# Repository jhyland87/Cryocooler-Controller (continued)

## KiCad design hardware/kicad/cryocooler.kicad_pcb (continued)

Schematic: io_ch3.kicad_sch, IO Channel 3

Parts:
C449: 100nF; C_0402_1005Metric
C450, C451: 1uF/50V; C_1206_3216Metric
D115, D116: TVS1800DRVR; WSON-6-1EP_2x2mm_P0.65mm_EP1x1.6mm
J38: IO3 (V+ / IO / GND / NC); XKB_X2510WRS-04-9TSN_1x04_P2.54mm_Horizontal
JP16: IO3 5V; R_0603_1608Metric
JP17: IO3 12V; R_0603_1608Metric; not fitted
Q103: CSD17381F4; Texas_FemtoFET_F4_1.0x0.6mm
R676, R683: 100k; R_0402_1005Metric
R677: 20k; R_0402_1005Metric
R678: 120; R_2512_6332Metric
R679: 1M; R_0402_1005Metric
R680: 53.6k; R_0402_1005Metric
R681: 10k; R_0402_1005Metric
R682: 22k; R_0402_1005Metric
U121: TPS26625DRCR; Texas_DRC0010J

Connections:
+3V3: R681.1; also elsewhere on the board
+5V: JP16.1 (A); also elsewhere on the board
+12V: JP17.1 (A); also elsewhere on the board
/Universal IO/IO3_ADC: C449.1, R676.2, R677.1; also elsewhere on the board
/Universal IO/IO3_BURDEN: Q103.1 (G), R683.1; also elsewhere on the board
/Universal IO/IO3_DIV: R677.2; also elsewhere on the board
/Universal IO/IO3_PIN: D116.4 (IN), D116.5 (IN), D116.6 (IN), J38.2, R676.1, R678.1; also elsewhere on the board
/Universal IO/IO3_SENS_EN: R682.1, U121.4 (~SHDN); also elsewhere on the board
/Universal IO/~IO3_SENS_FLT: R681.2, U121.9 (~FLT); also elsewhere on the board
GND: C449.2, C450.2, C451.2, D115.1 (GND), D115.2 (GND), D115.3 (GND), D115.7 (GND), D116.1 (GND), D116.2 (GND), D116.3 (GND), D116.7 (GND), J38.3, Q103.2 (S), R680.2, R682.2, R683.2, U121.3 (OVP), U121.5 (RTN), U121.6 (GND), U121.11 (EP); also elsewhere on the board
unnamed: C451.1, D115.4 (IN), D115.5 (IN), D115.6 (IN), J38.1, U121.10 (OUT)
unnamed: C450.1, JP16.2 (B), JP17.2 (B), R679.1, U121.1 (IN)
unnamed: Q103.3 (D), R678.2
unnamed: R680.1, U121.7 (ILIM)
unnamed: R679.2, U121.2 (UVLO)

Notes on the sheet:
Input: the pin through 100k to the ADC; with the 20k leg grounded (default) 15 V reads 2.5 V, with DIRECT high the range is 0-2.5 V. BURDEN adds 120 R for 4-20 mA loops; PULLUP (range switch sheet) adds 10k to +3V3.
SENSOR SUPPLY AND CONNECTOR
Universal I/O channel 3: connector pin 1 = switched sensor supply, 2 = signal, 3 = GND. Output: DAC level x 4.83 from a TSB582 section through a switch (IO Output Drivers sheet), up to 100 mA, open while OUT_EN is low.
Every control line is pulled to its off level, so the channel is high impedance with the sensor supply off until firmware sets the expander.
MEASUREMENT

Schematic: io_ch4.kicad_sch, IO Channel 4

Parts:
C452: 100nF; C_0402_1005Metric
C453, C454: 1uF/50V; C_1206_3216Metric
D117, D118: TVS1800DRVR; WSON-6-1EP_2x2mm_P0.65mm_EP1x1.6mm
J39: IO4 (V+ / IO / GND / NC); XKB_X2510WRS-04-9TSN_1x04_P2.54mm_Horizontal
JP18: IO4 5V; R_0603_1608Metric
JP19: IO4 12V; R_0603_1608Metric; not fitted
Q104: CSD17381F4; Texas_FemtoFET_F4_1.0x0.6mm
R684, R691: 100k; R_0402_1005Metric
R685: 20k; R_0402_1005Metric
R686: 120; R_2512_6332Metric
R687: 1M; R_0402_1005Metric
R688: 53.6k; R_0402_1005Metric
R689: 10k; R_0402_1005Metric
R690: 22k; R_0402_1005Metric
U122: TPS26625DRCR; Texas_DRC0010J

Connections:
+3V3: R689.1; also elsewhere on the board
+5V: JP18.1 (A); also elsewhere on the board
+12V: JP19.1 (A); also elsewhere on the board
/Universal IO/IO4_ADC: C452.1, R684.2, R685.1; also elsewhere on the board
/Universal IO/IO4_BURDEN: Q104.1 (G), R691.1; also elsewhere on the board
/Universal IO/IO4_DIV: R685.2; also elsewhere on the board
/Universal IO/IO4_PIN: D118.4 (IN), D118.5 (IN), D118.6 (IN), J39.2, R684.1, R686.1; also elsewhere on the board
/Universal IO/IO4_SENS_EN: R690.1, U122.4 (~SHDN); also elsewhere on the board
/Universal IO/~IO4_SENS_FLT: R689.2, U122.9 (~FLT); also elsewhere on the board
GND: C452.2, C453.2, C454.2, D117.1 (GND), D117.2 (GND), D117.3 (GND), D117.7 (GND), D118.1 (GND), D118.2 (GND), D118.3 (GND), D118.7 (GND), J39.3, Q104.2 (S), R688.2, R690.2, R691.2, U122.3 (OVP), U122.5 (RTN), U122.6 (GND), U122.11 (EP); also elsewhere on the board
unnamed: C454.1, D117.4 (IN), D117.5 (IN), D117.6 (IN), J39.1, U122.10 (OUT)
unnamed: C453.1, JP18.2 (B), JP19.2 (B), R687.1, U122.1 (IN)
unnamed: Q104.3 (D), R686.2
unnamed: R688.1, U122.7 (ILIM)
unnamed: R687.2, U122.2 (UVLO)

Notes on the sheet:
MEASUREMENT
SENSOR SUPPLY AND CONNECTOR
Universal I/O channel 4: connector pin 1 = switched sensor supply, 2 = signal, 3 = GND. Output: DAC level x 4.83 from a TSB582 section through a switch (IO Output Drivers sheet), up to 100 mA, open while OUT_EN is low.
Every control line is pulled to its off level, so the channel is high impedance with the sensor supply off until firmware sets the expander.
Input: the pin through 100k to the ADC; with the 20k leg grounded (default) 15 V reads 2.5 V, with DIRECT high the range is 0-2.5 V. BURDEN adds 120 R for 4-20 mA loops; PULLUP (range switch sheet) adds 10k to +3V3.

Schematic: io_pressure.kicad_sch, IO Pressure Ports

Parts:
C432, C433: 10nF; C_0402_1005Metric
D107, D108: TVS1800DRVR; WSON-6-1EP_2x2mm_P0.65mm_EP1x1.6mm
J32: PRESSURE 1 (5V / SIG / GND / NC); XKB_X2510WRS-04-9TSN_1x04_P2.54mm_Horizontal
J33: PRESSURE 2 (5V / SIG / GND / NC); XKB_X2510WRS-04-9TSN_1x04_P2.54mm_Horizontal
R636, R638: 2.2k; R_0402_1005Metric
R637, R639: 100k; R_0402_1005Metric

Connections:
/Universal IO/IO Pressure Ports/PRESS1_PIN: D107.4 (IN), D107.5 (IN), D107.6 (IN), J32.2, R636.1
/Universal IO/IO Pressure Ports/PRESS2_PIN: D108.4 (IN), D108.5 (IN), D108.6 (IN), J33.2, R638.1
/Universal IO/PREC_EXC: J32.1, J33.1; also elsewhere on the board
/Universal IO/PRESS1_ADC: C432.1, R636.2, R637.1; also elsewhere on the board
/Universal IO/PRESS2_ADC: C433.1, R638.2, R639.1; also elsewhere on the board
GND: C432.2, C433.2, D107.1 (GND), D107.2 (GND), D107.3 (GND), D107.7 (GND), D108.1 (GND), D108.2 (GND), D108.3 (GND), D108.7 (GND), J32.3, J33.3, R637.2, R639.2; also elsewhere on the board

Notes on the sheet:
Two ports for 3-wire pressure transmitters with a 0.5-4.5 V output on a 5 V supply (port 1: 100 psi ahead of the nitrogen membrane, port 2: 30 psi in the dewar). Pin 1 is the switched 5 V excitation shared with the precision ports.
The ADC reads each signal against REFP0 / REFN0, which is that same excitation, so the reading does not move with the 5 V rail. PGA bypassed. With nothing plugged in the 100k pull-down gives 0 V, below the 0.5 V a working sensor sends.
PRESSURE PORT 1 (100 PSI)
PRESSURE PORT 2 (30 PSI)

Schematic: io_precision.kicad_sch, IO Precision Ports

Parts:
C423, C424: 1uF; C_0603_1608Metric
C425, C428, C431: 100nF; C_0402_1005Metric
C426, C427, C429, C430: 10nF; C_0402_1005Metric
D102, D103, D104, D105, D106: TVS1800DRVR; WSON-6-1EP_2x2mm_P0.65mm_EP1x1.6mm
J30: SENSOR A (EXC / IN+ / IN- / GND); XKB_X2510WRS-04-9TSN_1x04_P2.54mm_Horizontal
J31: SENSOR B (EXC / IN+ / IN- / GND); XKB_X2510WRS-04-9TSN_1x04_P2.54mm_Horizontal
R626: 1M; R_0402_1005Metric
R627: 53.6k; R_0402_1005Metric
R628, R629: 1k; R_0402_1005Metric
R630, R631, R632, R633: 2.2k; R_0402_1005Metric
R634: 10k; R_0402_1005Metric
R635: 22k; R_0402_1005Metric
U109: TPS26625DRCR; Texas_DRC0010J

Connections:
+3V3: R634.1; also elsewhere on the board
+5V_IO: C423.1, R626.1, U109.1 (IN); also elsewhere on the board
/Universal IO/IO Precision Ports/PREC_A_N_PIN: D104.4 (IN), D104.5 (IN), D104.6 (IN), J30.3, R631.1
/Universal IO/IO Precision Ports/PREC_A_P_PIN: D103.4 (IN), D103.5 (IN), D103.6 (IN), J30.2, R630.1
/Universal IO/IO Precision Ports/PREC_B_N_PIN: D106.4 (IN), D106.5 (IN), D106.6 (IN), J31.3, R633.1
/Universal IO/IO Precision Ports/PREC_B_P_PIN: D105.4 (IN), D105.5 (IN), D105.6 (IN), J31.2, R632.1
/Universal IO/PREC_A_N: C427.1, C428.2, R631.2; also elsewhere on the board
/Universal IO/PREC_A_P: C426.1, C428.1, R630.2; also elsewhere on the board
/Universal IO/PREC_B_N: C430.1, C431.2, R633.2; also elsewhere on the board
/Universal IO/PREC_B_P: C429.1, C431.1, R632.2; also elsewhere on the board
/Universal IO/PREC_EXC: C424.1, D102.4 (IN), D102.5 (IN), D102.6 (IN), J30.1, J31.1, R628.1, U109.10 (OUT); also elsewhere on the board
/Universal IO/PREC_EXC_EN: R635.1, U109.4 (~SHDN); also elsewhere on the board
/Universal IO/PREC_REFN: C425.2, R629.2; also elsewhere on the board
/Universal IO/PREC_REFP: C425.1, R628.2; also elsewhere on the board
/Universal IO/~PREC_EXC_FLT: R634.2, U109.9 (~FLT); also elsewhere on the board
GND: C423.2, C424.2, C426.2, C427.2, C429.2, C430.2, D102.1 (GND), D102.2 (GND), D102.3 (GND), D102.7 (GND), D103.1 (GND), D103.2 (GND), D103.3 (GND), D103.7 (GND), D104.1 (GND), D104.2 (GND), D104.3 (GND), D104.7 (GND), D105.1 (GND), D105.2 (GND), D105.3 (GND), D105.7 (GND), D106.1 (GND), D106.2 (GND), D106.3 (GND), D106.7 (GND), J30.4, J31.4, R627.2, R629.1, R635.2, U109.3 (OVP), U109.5 (RTN), U109.6 (GND), U109.11 (EP); also elsewhere on the board
unnamed: R627.1, U109.7 (ILIM)
unnamed: R626.2, U109.2 (UVLO)

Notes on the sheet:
Two ports for sensors the universal channels suit badly: bridges (load cells, bare pressure sensors), RTDs, thermocouples, millivolt cells. Each has a differential pair straight into the ADS124S08 (port A: AIN8 / AIN9, port B: AIN10 / AIN11).
Inputs must stay between 0 V and 5 V. 2.2 k limits the current into the ADC to 3 mA with 12 V on a pin (10 mA allowed), so a wiring mistake does no damage; the reading of every ADC input is disturbed while it lasts. Excitation is off until PREC_EXC_EN is high.
EXCITATION AS THE ADC REFERENCE
PRECISION PORT A
EXCITATION (BOTH PORTS)
PRECISION PORT B
Gain, the 10 uA-2 mA current sources, the thermocouple bias and burn-out detection are ADC register settings. The 5 V excitation also feeds REFP0 / REFN0, so a bridge read against that reference ignores drift in the 5 V rail.

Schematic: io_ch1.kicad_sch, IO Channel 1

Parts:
C439, C442, C443: 100nF; C_0402_1005Metric
C440, C441: 1uF/50V; C_1206_3216Metric
D109: 1N4148W; D_SOD-123
D110, D111: TVS1800DRVR; WSON-6-1EP_2x2mm_P0.65mm_EP1x1.6mm
J36: IO1 (V+ / IO / GND / NC); XKB_X2510WRS-04-9TSN_1x04_P2.54mm_Horizontal
JP12: IO1 5V; R_0603_1608Metric
JP13: IO1 12V; R_0603_1608Metric; not fitted
Q101: CSD17381F4; Texas_FemtoFET_F4_1.0x0.6mm
R650, R660, R662: 100k; R_0402_1005Metric
R651: 20k; R_0402_1005Metric
R652: 120; R_2512_6332Metric
R653, R656: 1M; R_0402_1005Metric
R654, R655: 1k; R_0402_1005Metric
R657: 53.6k; R_0402_1005Metric
R658, R661: 10k; R_0402_1005Metric
R659: 22k; R_0402_1005Metric
U115: SN74LVC1G3157DSFR; Texas_DSF0006A_X2SON-6_1x1mm_P0.35mm
U116: SN74LVC1G125DRYR; Texas_USON-6_1x1.45mm_P0.5mm_SMD
U117: TPS26625DRCR; Texas_DRC0010J

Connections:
+3V3: C442.1, C443.1, D109.1 (K), R658.1, R661.1, U115.5 (VCC), U116.6 (VCC); also elsewhere on the board
+5V: JP12.1 (A); also elsewhere on the board
+12V: JP13.1 (A); also elsewhere on the board
/AUX_IO5: R654.2, R655.1; also elsewhere on the board
/Universal IO/IO1_ADC: C439.1, R650.2, R651.1; also elsewhere on the board
/Universal IO/IO1_BURDEN: Q101.1 (G), R660.1; also elsewhere on the board
/Universal IO/IO1_DAC: U115.1 (B2); also elsewhere on the board
/Universal IO/IO1_DIV: R651.2; also elsewhere on the board
/Universal IO/IO1_LEVEL: U115.4 (A); also elsewhere on the board
/Universal IO/IO1_PIN: D111.4 (IN), D111.5 (IN), D111.6 (IN), J36.2, R650.1, R652.1, R653.1; also elsewhere on the board
/Universal IO/IO1_SENS_EN: R659.1, U117.4 (~SHDN); also elsewhere on the board
/Universal IO/IO Channel 1/IO1_BUF: R654.1, U116.4 (Y)
/Universal IO/IO Channel 1/IO1_GATE: R655.2, R662.1, U115.6 (S)
/Universal IO/IO Channel 1/IO1_LOGIC: D109.2 (A), R653.2, U116.2 (A)
/Universal IO/~IO1_BUF_OE: R661.2, U116.1 (~OE); also elsewhere on the board
/Universal IO/~IO1_SENS_FLT: R658.2, U117.9 (~FLT); also elsewhere on the board
GND: C439.2, C440.2, C441.2, C442.2, C443.2, D110.1 (GND), D110.2 (GND), D110.3 (GND), D110.7 (GND), D111.1 (GND), D111.2 (GND), D111.3 (GND), D111.7 (GND), J36.3, Q101.2 (S), R657.2, R659.2, R660.2, R662.2, U115.2 (GND), U115.3 (B1), U116.3 (GND), U117.3 (OVP), U117.5 (RTN), U117.6 (GND), U117.11 (EP); also elsewhere on the board
unnamed: C441.1, D110.4 (IN), D110.5 (IN), D110.6 (IN), J36.1, U117.10 (OUT)
unnamed: C440.1, JP12.2 (B), JP13.2 (B), R656.1, U117.1 (IN)
unnamed: Q101.3 (D), R652.2
unnamed: R657.1, U117.7 (ILIM)
unnamed: R656.2, U117.2 (UVLO)

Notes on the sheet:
Input: the pin through 100k to the ADC; with the 20k leg grounded (default) 15 V reads 2.5 V, with DIRECT high the range is 0-2.5 V. BURDEN adds 120 R for 4-20 mA loops; PULLUP (range switch sheet) adds 10k to +3V3.
OUTPUT GATE (GPIO5)
SENSOR SUPPLY AND CONNECTOR
GATE AND BUFFER DECOUPLING CAPACITORS
Every control line is pulled to its off level, so the channel is high impedance with the sensor supply off until firmware sets the expander. GPIO5 gates the DAC level (PWM) and reads the pin through the buffer.
FAST PATH (GPIO5)
MEASUREMENT
Universal I/O channel 1: connector pin 1 = switched sensor supply, 2 = signal, 3 = GND. Output: DAC level x 4.83 from a TSB582 section through a switch (IO Output Drivers sheet), up to 100 mA, open while OUT_EN is low.

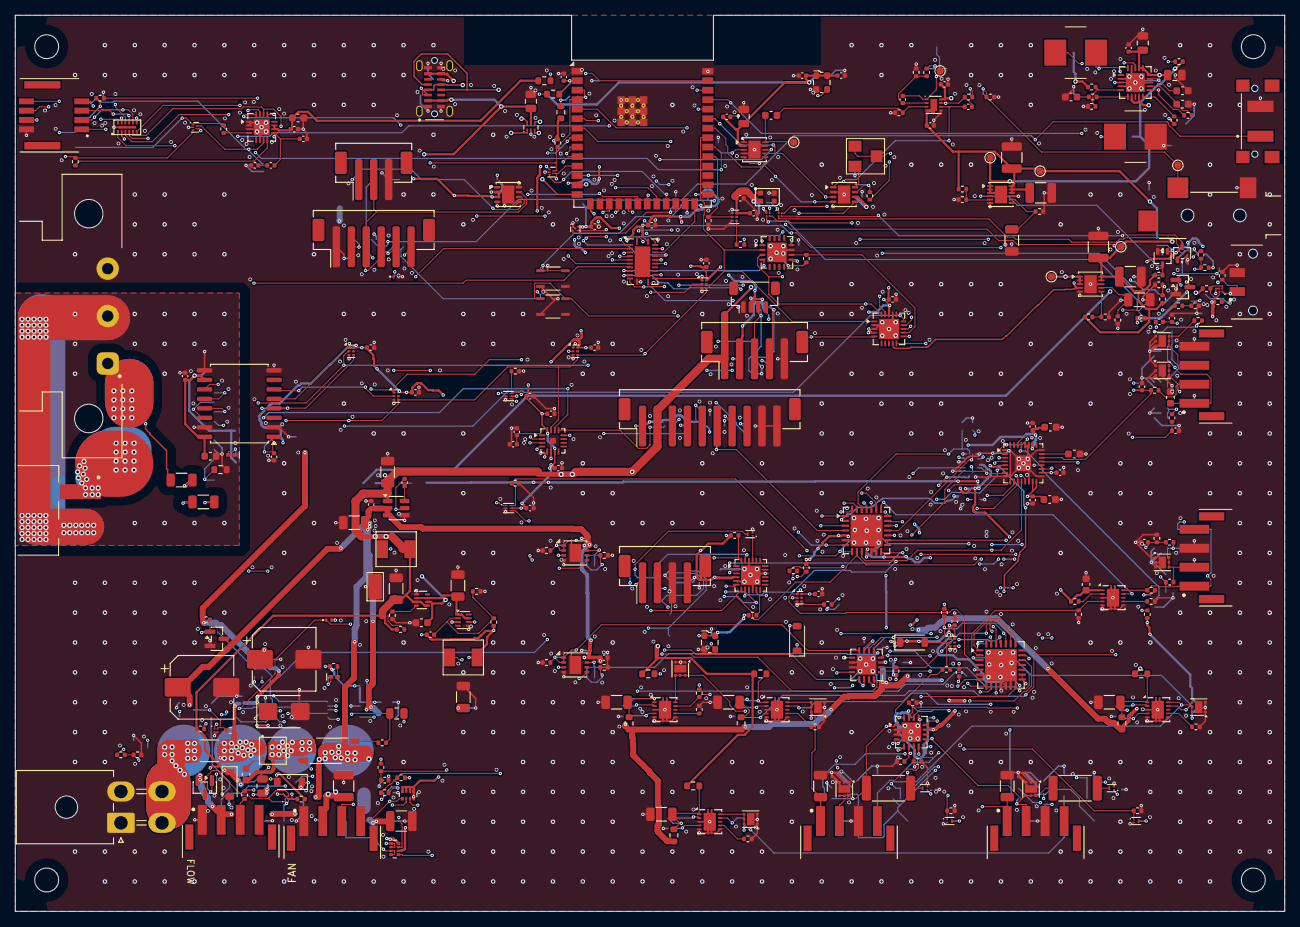
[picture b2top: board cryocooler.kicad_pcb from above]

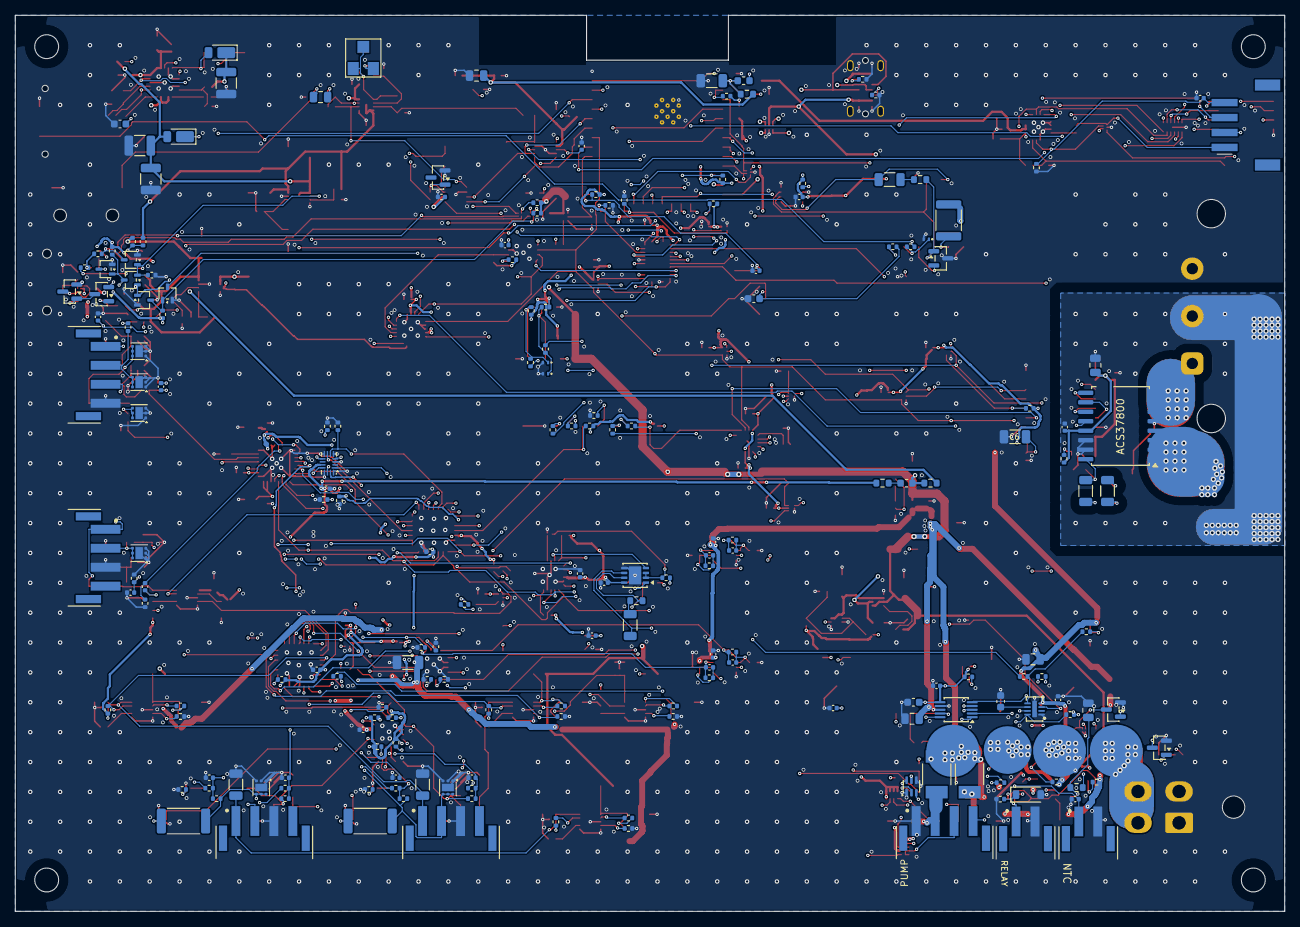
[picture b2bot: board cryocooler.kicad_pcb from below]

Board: 4 copper layers, 170.0 x 120.0 mm, 502 parts (193 on the bottom side), 313 nets.

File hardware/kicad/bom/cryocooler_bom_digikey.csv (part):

Quantity,Manufacturer Part Number,Manufacturer,Description,Customer Reference,Value,Package,MPN basis,Notes
6,CL31A226KPHNNNE,Samsung Electro-Mechanics,CAP CER 22UF 10V X5R 1206,C1-C6,22uF/10V,C_1206_3216Metric,suggested,"5 V and 3.3 V buck outputs, ISOW7741 VDD and VISOOUT, ESP32"
6,CL21A106KACLRNC,Samsung Electro-Mechanics,CAP CER 10UF 25V X5R 0805,C7-C12,10uF,C_0805_2012Metric,ordered,substitute for CL21A106KAYNNNE
60,CL05B104KB54PNC,Samsung Electro-Mechanics,CAP CER 0.1UF 50V X7R 0402,C13-C20 C23-C35 C39 C40 C52 C53 C301 C302 C305-C307 C401 C402 C404 C405 C407 C409 C410 C415 C416 C418-C422 C425 C428 C431 C434-C439 C442-C444 C447-C449 C452,100nF,C_0402_1005Metric,suggested,
14,CL10A105KB8NNNC,Samsung Electro-Mechanics,CAP CER 1UF 50V X5R 0603,C41-C46 C48-C50 C403 C406 C408 C423 C424,1uF,C_0603_1608Metric,suggested,
1,CL10B683KB8NNNC,Samsung Electro-Mechanics,CAP CER 0.068UF 50V X7R 0603,C55,68nF,C_0603_1608Metric,suggested,ADP5071 COMP2
7,GRM32ER71E226KE15L,Murata,CAP CER 22UF 25V X7R 1210,C56-C62,22uF/25V X7R,C_1210_3225Metric,suggested,"ADP5071 outputs / regulator inputs and the +-15 V outputs; the LT3045 / LT3094 need >= 10 uF effective at 15 V DC bias (INN and both outputs have two in parallel; INP needs 4.7 uF), so check the DC-bias curve"
1,C2012X5R1E475K085AC,TDK,CAP CER 4.7UF 25V X5R 0805,C63,4.7uF,C_0805_2012Metric,ordered,USB VBUS filter; substitute for CL21A475KAQNNNE
1,EEE-FK1V101P,Panasonic,CAP ALUM 100UF 20% 35V SMD 8x10.2,C65,100uF/35V,CP_Elec_8x10,suggested,"C65 sits on the input rail behind a 26 V TVS clamp; rating taken from distributor listings, not a Panasonic datasheet"
1,EEE-FK1E101AP,Panasonic,CAP ALUM 100UF 20% 25V SMD 8x10.2,C66,100uF/25V,CP_Elec_8x10,ordered,switched +12 V rail; substitute for EEE-FK1E101P
2,CL21B104KBCNNNC,Samsung Electro-Mechanics,CAP CER 0.1UF 50V X7R 0805,C67 C68,100nF,C_0805_2012Metric,suggested,
9,CL05B103KB5NNNC,Samsung Electro-Mechanics,CAP CER 10000PF 50V X7R 0402,C69-C71 C426 C427 C429 C430 C432 C433,10nF,C_0402_1005Metric,suggested,
2,C1210C226K3PACTU,Kemet,CAP CER 22UF 25V X5R 1210,C76 C77,22uF/25V,C_1210_3225Metric,ordered,12 V rail; substitute for CL32A226KAJNNNE
1,CL31A106KBHNNNE,Samsung Electro-Mechanics,CAP CER 10UF 50V X5R 1206,C78,10uF/50V,C_1206_3216Metric,suggested,12 V rail (U15 input); 50 V so it is rated over the SMBJ16A clamp (about 26 V); JLCPCB C13585 (basic)
2,CL10B473KB8NNNC,Samsung Electro-Mechanics,CAP CER 0.047UF 50V X7R 0603,C79 C80,47nF,C_0603_1608Metric,suggested,ADP5071 COMP1; Q1 gate-drain slow start
10,CL31B105KBHNNNE,Samsung Electro-Mechanics,CAP CER 1UF 50V X7R 1206,C81 C82 C440 C441 C445 C446 C450 C451 C453 C454,1uF/50V,C_1206_3216Metric,suggested,LT3045 / LT3094 SET bypass (the pins sit at 14.7 V DC)
2,CL21B474KBFNNNE,Samsung Electro-Mechanics,CAP CER 0.47UF 50V X7R 0805,C83 C84,470nF,C_0805_2012Metric,suggested,INA239 input filter across IN+/IN-; Q1 gate-source
1,CL05C102JB5NNNC,Samsung Electro-Mechanics,CAP CER 1000PF 50V C0G 0402,C85,1nF/C0G,C_0402_1005Metric,suggested,across R35 + R92 (50.6k) in the sine gain stage
1,CL05C220JB5NNNC,Samsung Electro-Mechanics,CAP CER 22PF 50V C0G 0402,C86,22pF/C0G,C_0402_1005Metric,suggested,"AD5453 output stage stability (datasheet C1), sized for the OPA2991"
1,CL05C121JB5NNNC,Samsung Electro-Mechanics,CAP CER 120PF 50V C0G 0402,C87,120pF,C_0402_1005Metric,suggested,TPS62822 feed-forward across the 453k
1,CL21B225KAFNNNE,Samsung Electro-Mechanics,CAP CER 2.2UF 25V X7R 0805,C400,2.2uF,C_0805_2012Metric,suggested,auto power-on capacitor on the LTC2954 PB pin; stock not checked
4,CL05C020CB5NNNC,Samsung Electro-Mechanics,CAP CER 2PF 50V C0G 0402,C411-C414,2pF/C0G,C_0402_1005Metric,suggested,AD5453 output stage stability (datasheet C1)
1,C3216X5R1E106K085AC,TDK,CAP CER 10UF 25V X5R 1206,C417,10uF/25V,C_1206_3216Metric,ordered,12 V rail; substitute for CL31A106KAHNNNE
1,SMBJ16A,Littelfuse,TVS DIODE 16VWM 26VC DO214AA,D1,SMBJ16A,D_SMB,design,unidirectional
5,APGB0607G22R23C,Kingbright,LED GREEN/RED BICOLOR 0.65X0.65MM SMD,D2 D3 D7 D11 D12,APGB0607G22R23C,LED_Kingbright_APGB0607,design,"two-state indicators; independent dies, about 1 mA each"
2,DFLS240-7,Diodes Incorporated,DIODE SCHOTTKY 40V 2A POWERDI123,D4 D5,DFLS240,D_PowerDI-123,design,
1,APHHS1005SURCK,Kingbright,LED RED (630 NM) CLEAR 0402 SMD,D6,APHHS1005SURCK,LED_Kingbright_APHHS1005,design,"D6 INA239 ALERT, about 0.9 mA (1.5k on 3.3 V); Vf 1.95 V typ at 20 mA"
1,APHHS1005LZGCK-V,Kingbright,LED GREEN (525 NM) CLEAR 0402 SMD,D10,APHHS1005LZGCK-V,LED_Kingbright_APHHS1005,design,"D10 isolated 5 V rail, about 0.7 mA (3.3k on 5 V); Vf 2.65 V typ at 2 mA; InGaN, 450 V HBM"
1,4684,Adafruit,LED RGB NEOPIXEL NANO WS2812B-2020 2 X 2 MM (10 pack),D13,WS2812B-2020,LED_WS2812B-2020_PLCC4_2.0x2.0mm,design,Adafruit listed the 10 pack out of stock on 2026-11-06; the 100 pack is Adafruit 6428. Check JLCPCB/LCSC for a WS2812B-2020 if you assemble there
4,1N4148W-7-F,Diodes Incorporated,DIODE GEN PURP 75V 150MA SOD123,D14 D100 D109 D112,1N4148W,D_SOD-123,design,
1,BAT54AW-7-F,Diodes Incorporated,DIODE ARR SCHOTTKY 30V 200MA SOT323,D15,BAT54AW,SOT-323_SC-70,design,"common anode on PG_15V (pin 3), cathodes on pins 1 and 2"
1,MMBZ9V1ALT1G,onsemi,TVS DIODE 6VWM DUAL COMMON ANODE SOT23-3,D16,MMBZ9V1ALT1G,SOT-23,design,"AD5453 VREF clamp: used between cathodes, under 10.5 V"
1,BZT52C15-7-F,Diodes Incorporated,DIODE ZENER 15V 500MW SOD123,D17,BZT52C15,D_SOD-123,suggested,"Q1 gate clamp, 13.8-15.6 V"
1,ESD2CAN24DBZRQ1,Texas Instruments,TVS DIODE 24VWM CAN 2CH SOT23,D101,ESD2CAN24DBZR,SOT-23,design,CAN bus clamp at the display connector; no leadless CAN clamp was in stock
15,TVS1800DRVR,Texas Instruments,TVS DIODE 18VWM 6WSON,D102-D108 D110 D111 D113-D118,TVS1800DRVR,WSON-6-1EP_2x2mm_P0.65mm_EP1x1.6mm,design,"surge clamps at the universal I/O and precision port connectors (21 needed); over 1,000 at Digi-Key (checked by the user, 2026-11-16), 50 at Mouser"
1,0453010.MR,Littelfuse,FUSE BRD MNT 10A 125VAC/VDC 2SMD,F1,10A backup,Fuse_Littelfuse-NANO2-451_453,suggested,"NANO2 453 series, fast acting, same 2410 land as the 5 A part it replaces; backup only: add a fuse at the PSU end. Stock not checked"
1,MF-MSMF050/24X-2,Bourns,PTC RESET FUSE 24V 500MA 1812,F2,MF-MSMF050/24X,Fuse_1812_4532Metric,design,"display feed: 0.5 A hold, 1 A trip; the display draws about 0.2 A"
1,MF-MSMF050/24X-2,Bourns,PTC RESET FUSE 24V 500MA 1812,F3,MF-MSMF050/24X,Bourns_MF-MSMF_1812_4532Metric,design,"F3 fan header +12 V: 0.5 A hold (0.40 A at 50 C), 1 A trip; 3 fans draw 0.15 A max. Bourns land pattern (F2 uses the KiCad 1812 footprint)"
1,MF-MSMF250/16X-2,Bourns,PTC RESET FUSE 16V 2.5A 1812,F4,MF-MSMF250/16X,Bourns_MF-MSMF_1812_4532Metric,design,"F4 pump header +12 V: 2.5 A hold (1.98 A at 50 C), 5 A trip; pump draws up to 1.5 A. Digi-Key stock figures were not confirmed"
2,BLM18PG121SN1D,Murata,FERRITE BEAD 120 OHM 100MHZ 2A 0603,FB3 FB4,BLM18PG121SN1D,L_0603_1608Metric,suggested,ahead of JP5 on the cold head supply; rating from distributor listings
1,USB4210-GF-A,GCT,"USB-C 2.0 RECEPTACLE 16P, FLAG TYPE, TOP MOUNT",J1,USB_C,USB_C_Receptacle_GCT_USB4205-GF-A_16P_Flag,design,"J1: stands on its side, 9.89 mm high, mouth 3 mm past the board edge; four plated shell stakes and two pegs. Same land pattern as the 12.5 mm USB4205-GF-A the footprint is named after (GCT drawing USB4210 rev A2)"
1,39-30-0040,Molex,CONN HEADER R/A 4POS 4.2MM MINI-FIT JR,J2,,Molex_Mini-Fit_Jr_5569-04A2_2x02_P4.20mm_Horizontal,design,"J2 12 V in, pinned as the ATX 12 V (CPU) connector: 1 and 2 ground, 3 and 4 +12 V; mates with housing 39-01-2040. Part number taken from the KiCad footprint; stock not checked. Check the cable polarity with a meter before first use"
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
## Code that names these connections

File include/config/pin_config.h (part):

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// USB-JTAG) and GPIO45 low at reset. GPIO44 is U0RXD; the console is native USB
// CDC, so UART0 is unused. GPIO47 swings 1.8 V only, so address bit D reaches the
// decoder through a 74LV1T34 buffer whose input pull-down reads 0 while it floats.
#define CS_ADDR_A_PIN      3
#define CS_ADDR_B_PIN      44
#define CS_ADDR_C_PIN      45
#define CS_ADDR_D_PIN      47
#define CS_ENABLE_PIN      8

// *_CS values below are not GPIOs: src/spi_select.cpp catches these IDs in
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
// MCP23S08 SPI GPIO expander — SPI mode 0 on the shared SPI bus. See the
// EXPANDER_PIN_* map below. RESET is tied high; INT is not wired to the MCU.
#define EXPANDER_CS_PIN    (CS_ID_BASE + 3)

// AD5453 14-bit multiplying DAC — amplitude control. SPI mode 1, writes only.
#define AD5453_SYNC        (CS_ID_BASE + 1)

// INA239 power monitor — SPI mode 1 on the shared SPI bus (MISO is Hi-Z when CS is high).
#define INA239_CS          (CS_ID_BASE + 2)

// ADS1220 RTD ADC — SPI mode 1 on the shared SPI bus (DOUT is Hi-Z when CS is high).
// DRDY is not wired to the MCU.
#define ADS1220_CS         (CS_ID_BASE + 6)

// LSM6DSOX IMU — Adafruit breakout (product 4438) mounted on the cryocooler and
// cabled to header J14; SPI on the shared bus (AD9833, AD5453, ...).
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
// ADT7320 ambient temperature sensor (U50) — SPI mode 3, MSB first, DOUT is released
// after CS rises. INT and CT (open drain, 10 kOhm pull-ups) go to expander GP2 and GP3.
#define AMBIENT_CS         (CS_ID_BASE + 8)
// IDs CS_ID_BASE + 9 to CS_ID_BASE + 15 are spare decoder outputs (Y9 to Y15).
#define LSM6DSOX_INT1_PIN  2    // J14 pin 7
#define LSM6DSOX_INT2_PIN  39   // J14 pin 8
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// LTC2954 power button handshake. INT# pulses low (32 ms minimum, 10 kOhm
// pull-up R8) when the button asks for power-off; driving KILL# low releases
// the supply. The LTC2954 cuts power by itself if the button is held 6.4 s.
#define PWR_INT_PIN       1
#define PWR_KILL_PIN      10

// =============================================================================
// SPI Bus (AD9833, AD5453, LSM6DSOX, INA239, ADS1220, MCP23S08, ST7789V, TSC2046,
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// =============================================================================
// Why am I not using values from /Users/justinhyland/.platformio/packages/framework-arduinoespressif32/variants/esp32s3/pins_arduino.h?
// or /Users/justinhyland/.platformio/packages/framework-arduinoespressif32/variants/esp32_s3r8n16/pins_arduino.h
#define SPI_MISO          40    // Master In Slave Out  (read by the LSM6DSOX, INA239, ADS1220 and ACS37800)
#define SPI_MOSI          41    // Master Out Slave In  (AD5453 SDIN + AD9833 SDATA + LSM6DSOX SDI + INA239 MOSI)
#define SPI_CLK           42    // SPI Clock


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// Each pin has a 100 Ohm series resistor, 200 kOhm to ground, an ESD clamp and an
// indicator LED whose brightness follows the pin voltage. Only GPIO5 and GPIO7 are
// ADC1 and can read analog with WiFi on; GPIO11 to GPIO13 are ADC2.
#define AUX_IO5_PIN        5
#define AUX_IO7_PIN        7
#define AUX_IO11_PIN       11
#define AUX_IO12_PIN       12
#define AUX_IO13_PIN       13

// =============================================================================
// Alphacool ES High Flow + Temperature Sensor
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// Not yet applied above, because the display and ACS37800 firmware change with
// them: on rev 5 ACS37800_CS is CS_ID_BASE + 5, the on-board display is gone
// (DISP_*, TOUCH_CS_PIN, EXPANDER_PIN_DISP_BL, EXPANDER_PIN_TOUCH_IRQ) and
// AUX_IO12_PIN is CAN_RX. IO_DAC_CS reuses the old display ID.
#define CAN_TX_PIN                   17  // TCAN3414 TXD (10 kOhm pull-up)
#define CAN_RX_PIN                   12  // TCAN3414 RXD

// Universal I/O (four channels): DAC60508 (SPI mode 1), ADS124S08 (SPI mode 1), two
// MCP23S17 (hardware addresses 0 and 1, one chip select).
#define IO_DAC_CS                    (CS_ID_BASE + 4)
#define IO_ADC_CS                    (CS_ID_BASE + 9)
#define IO_EXPANDER_CS               (CS_ID_BASE + 10)
// SC16IS750 UART for the RS-485 port: SPI mode 0, 4 MHz max.
#define RS485_UART_CS                (CS_ID_BASE + 11)
// SPI expansion header chip selects A and B. IDs + 14 and + 15 are spare.
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
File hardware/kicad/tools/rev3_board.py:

"""Brings the routed UCS 145-125 board to the rev 3 schematic: removes retired parts, swaps
changed footprints, places new parts, syncs pad nets, renames nets whose copper still
fits, and rips copper on nets that changed. Close the open ends with `gen_pcb.py link`,
`gridroute.py` on the DRC report, then the later rev 3 steps in hardware/HANDOFF_rev3.md.

Parts use the reference numbers from before the rev 3 renumber, so run this before
`renumber_refs.py board`. It was run once on the rev 2 board; the placement tables are
kept as the record of what moved.

Usage: rev3_board.py in.kicad_pcb out.kicad_pcb
"""
import json
import math
import sys
from pathlib import Path

import pcbnew

import pcbnetlist
from spi_expander_board import KEEP, add_part, clear_copper_under, net_of, place

MM = pcbnew.FromMM

# Nets whose copper still fits one new net.
RENAMES = {
    'Net-(J10-Pin_1)': 'RTD_1',
    'Net-(J10-Pin_2)': 'RTD_2',
    'Net-(J10-Pin_3)': 'RTD_3',
    'Net-(J10-Pin_4)': 'RTD_4',
    'ISO_3V3': 'ISO_5V',
    'Net-(D7-K)': 'INA239_ALERT',
    'Net-(U11-~{INT})': 'PWR_INT',
    'MCP4921_CS': 'AD5453_SYNC',
    'Net-(Q1-G)': 'Net-(U11-~{EN})',
}
CLEARANCE = 0.16
PLACEMENT_FILE = Path(__file__).with_name('rev3_placement.json')


def load_placement():
    """Returns ref -> [x, y, rotation, bottom], ripped boxes and removed zones."""
    return json.loads(PLACEMENT_FILE.read_text())


def ends(item):
    if item.Type() == pcbnew.PCB_VIA_T:
        return [item.GetPosition()]
    return [item.GetStart(), item.GetEnd()]


def inside(point, box):
    return box[0] <= point.x / 1e6 <= box[2] and box[1] <= point.y / 1e6 <= box[3]


def drop(board, item):
    KEEP.append(item)
    board.Remove(item)


def remove_retired(board, parts):
    for footprint in list(board.GetFootprints()):
        ref = footprint.GetReference()
        if ref and ref not in parts:
            drop(board, footprint)


def swap_footprints(board, parts, spots):
    """Replaces every part whose footprint changed; keeps its spot unless spots says."""
    swapped = {}
    for footprint in list(board.GetFootprints()):
        ref = footprint.GetReference()
        if not ref or ref not in parts:
            continue
        name = parts[ref]['footprint'].split(':')[-1]
        if str(footprint.GetFPID().GetLibItemName()) == name:
            continue
        spot = spots.get(ref, [
            footprint.GetX() / 1e6, footprint.GetY() / 1e6,
            footprint.GetOrientationDegrees(), footprint.IsFlipped()])
        drop(board, footprint)
        swapped[ref] = add_part(board, ref, parts[ref], spot)
    return swapped


def rip(board, spec):
    """Removes copper: spec is [box, nets]; nets '*' means every net but GND."""
    box, nets = spec
    for item in list(board.GetTracks()):
        name = item.GetNetname()
        wanted = (name not in ('GND', 'ISO_GND')) if nets == '*' else name in nets
        if wanted and any(inside(point, box) for point in ends(item)):
            drop(board, item)


def segment_gap(point, start, end):
    """Distance in nm from a point to a segment."""
    delta_x, delta_y = end[0] - start[0], end[1] - start[1]
    length = delta_x * delta_x + delta_y * delta_y
    ratio = 0 if not length else max(0, min(1, (
        (point[0] - start[0]) * delta_x + (point[1] - start[1]) * delta_y) / length))
    return math.hypot(point[0] - start[0] - ratio * delta_x, point[1] - start[1] - ratio * delta_y)


def clear_along(board, net, layer, width, start, end):
    """Rips other nets' copper within clearance of a new track."""
    margin = width / 2 + MM(CLEARANCE)
    steps = max(1, int(math.dist(start, end) / MM(0.05)))
    samples = [(start[0] + (end[0] - start[0]) * step / steps,
                start[1] + (end[1] - start[1]) * step / steps) for step in range(steps + 1)]
    for item in list(board.GetTracks()):
        if item.GetNetname() == net:
            continue
        if item.Type() == pcbnew.PCB_VIA_T:
            where = item.GetPosition()
            reach = margin + item.GetWidth(pcbnew.F_Cu) / 2
            hit = any(math.dist(sample, (where.x, where.y)) < reach for sample in samples)
        else:
            if item.GetLayer() != layer:
                continue
            first, second = item.GetStart(), item.GetEnd()
            reach = margin + item.GetWidth() / 2
            hit = any(segment_gap(sample, (first.x, first.y), (second.x, second.y)) < reach
                      for sample in samples)
        if hit:
            drop(board, item)


def add_copper(board, plan):
    """Draws the hand-placed power copper, clearing whatever crosses it."""
    for net, layer_name, width, points in plan['tracks']:
        layer = board.GetLayerID(layer_name)
        for first, second in zip(points, points[1:]):
            start = (MM(first[0]), MM(first[1]))
            end = (MM(second[0]), MM(second[1]))
            clear_along(board, net, layer, MM(width), start, end)
            track = pcbnew.PCB_TRACK(board)
            track.SetStart(pcbnew.VECTOR2I(*start))
            track.SetEnd(pcbnew.VECTOR2I(*end))
            track.SetLayer(layer)
            track.SetWidth(MM(width))
            track.SetNet(net_of(board, net))
            board.Add(track)
            KEEP.append(track)
    for net, pos_x, pos_y, diameter, drill in plan['vias']:
        spot = (MM(pos_x), MM(pos_y))
        clear_along(board, net, board.GetLayerID('F.Cu'), MM(diameter), spot, spot)
        clear_along(board, net, board.GetLayerID('In2.Cu'), MM(diameter), spot, spot)
        clear_along(board, net, board.GetLayerID('B.Cu'), MM(diameter), spot, spot)
        via = pcbnew.PCB_VIA(board)
        via.SetPosition(pcbnew.VECTOR2I(*spot))
        via.SetViaType(pcbnew.VIATYPE_THROUGH)
        via.SetWidth(MM(diameter))
        via.SetDrill(MM(drill))
        via.SetNet(net_of(board, net))
        board.Add(via)
        KEEP.append(via)


def main():
    source, target = sys.argv[1:3]
    parts, nets = pcbnetlist.load_netlist()
    plan = load_placement()
    spots = plan['parts']
    board = pcbnew.LoadBoard(source)
    pin_net = {(ref, pin): name for name, nodes in nets.items() for ref, pin in nodes}

    remove_retired(board, parts)
    swapped = swap_footprints(board, parts, spots)
    present = {footprint.GetReference() for footprint in board.GetFootprints()}
    for ref in sorted(set(parts) - present):
        add_part(board, ref, parts[ref], spots.get(ref, [125.0, 50.0, 0, False]))
    for ref, spot in spots.items():
        place(board.FindFootprintByReference(ref), *spot)

    for zone in list(board.Zones()):
        name = zone.GetNetname()
        box = plan['removed_plus3v3_box']
        first = zone.Outline().CVertex(0)
        old_tab_pour = name == '+3V3' and zone.GetLayer() == pcbnew.F_Cu and inside(first, box)
        if name in plan['removed_zones'] or old_tab_pour:
            drop(board, zone)

    for item in list(board.GetTracks()):
        name = item.GetNetname()
        name = RENAMES.get(name, name)
        if name not in nets:
            drop(board, item)
        else:
            item.SetNet(net_of(board, name))
    for spec in plan['rips']:
        rip(board, spec)

    no_net = board.FindNet(0)
    for footprint in board.GetFootprints():
        ref = footprint.GetReference()
        if ref not in parts:
            continue
        footprint.SetValue(parts[ref]['value'])
        for pad in footprint.Pads():
            name = pin_net.get((ref, pad.GetNumber()))
            pad.SetNet(net_of(board, name) if name else no_net)

    add_copper(board, plan)
    cut = set()
    for ref in sorted(set(spots) | set(swapped) | (set(parts) - present)):
        cut |= clear_copper_under(board, board.FindFootprintByReference(ref))
    print('cut by moved parts:', sorted(cut))
    pcbnew.ZONE_FILLER(board).Fill(board.Zones())
    board.Save(target)


if __name__ == '__main__':
    main()

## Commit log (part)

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2026-02-21 Adding on durration to telemetry
2026-02-21 telemetry update
2026-02-21 dashboard
2026-02-21 Telemetry
2026-02-21 serial commands
2026-02-21 State machine
2026-02-22 Adding ambient temperature sensor and rms logic
2026-02-22 Lots of changes
2026-02-23 Telemetry FrameBuilder class, ACS712 non blocking updates, misc
2026-02-23 Renaming the ACS712 lib
2026-02-23 Adding JSON output for web, adding readme
2026-02-23 Adding docs
2026-02-23 These are not the droids you are looking for.
2026-02-23 Tests
2026-02-24 Add ContinuousZMCT103C as git submodule
2026-02-24 Removing continuous ac712
2026-02-24 Shutdown logic
2026-02-25 accelerometer
2026-02-25 Creating a serial studio dashboard generator, creating the tcp socket for it
2026-02-25 misc
2026-02-26 Damn, this was a lot
2026-02-26 Renamed the device dashboard submodule
2026-02-26 Adding the base module for the cooling pump
2026-02-26 weefee
2026-02-26 Averaging the delta-temp. Adding a hostname.
2026-02-26 dash
2026-02-27 cooling stuff
2026-02-27 Dependencies
2026-02-27 stuff
2026-02-27 Removing the index dependency for the dashboard
2026-02-28 adding some i2c changes, and misc
2026-02-28 Integration hell
2026-02-28 rm irrelevant stuff
2026-02-28 Having telemetry and dashboard init first
2026-03-01 FSM overhall
2026-03-01 Fixing fsm
2026-03-01 Mock data stuff
2026-03-01 submodule
2026-03-01 Finite state machine updates
2026-03-02 More mocks, and other updates
2026-03-02 Moving DAC, Waveform and RMS modules into a single Amplifier module. And other stuff
2026-03-02 Adding new amplifier module, and a ton of other changes
2026-03-02 getting it working
2026-03-02 so irritated
2026-03-03 working, and cleaning it up
2026-03-03 Disabling the gyroscope, renaming variables
2026-03-03 Working on FSM
2026-03-04 Adding the tracking monitor poc code. Untested
2026-03-04 adding logging to sd card
2026-03-05 fixing tracking
2026-03-06 Many a changes
2026-03-06 OTA Updates ftw
2026-03-06 Switching the DAC, and removing the ADC
2026-03-06 No more waiting on serial
2026-03-06 millis
2026-03-06 espnow
2026-03-07 Fixing fsm, moving dependency check to fsm start state prechecks
2026-03-08 Switching out some of the modules; fixing mock;
2026-03-08 WIP - Broken
2026-03-08 Current code with mock and dependency check refactor
2026-03-09 Fault handling refactor
2026-03-09 More refactoring, cleaning up
2026-03-09 Dashboard 2.0
2026-03-09 blah
2026-03-09 Dashboard is kinda workin
2026-03-10 Getting relay working
2026-03-11 Fixing a few things.
2026-03-11 Fixing the fam/pump rpm readings
2026-03-11 Adding logs to http output
2026-03-11 Fixing the serial bug. No thanks to AI, jeez
2026-03-11 works great
2026-03-11 Getting everything to use celcius, no kelvin
2026-03-12 Workin out the bugs; switched the relay module
2026-03-12 New telemetry format
2026-03-12 Implementing telemetry updates and misc formatting changes
2026-03-12 simplifying jsx components
2026-03-13 Pump speed fix
2026-03-13 Implementing custom RTD methods
2026-03-13 adding submodule
2026-03-13 Updating SerialStudio dash
2026-03-13 not working yet
2026-03-13 Fixing the faults in dashboad, and a fsm state loop
2026-03-13 Fixing cooling
2026-03-14 not totally working yet.
2026-03-15 Working
2026-03-15 Minor updates
2026-03-15 it wooorkss
2026-03-17 Updating dashboard, fixing a few things, changing the voltage based logic to fractions
2026-03-17 Adding reconnect wrapper.
2026-03-18 Reconnect logic, and other fixes
2026-03-18 telemetry updates
2026-03-20 Updating UI styles
2026-03-20 Faster loading dashboard
2026-03-20 updating dashboard related stuff
2026-03-21 implementing different RTD sensor
2026-03-22 Clearing temp on startup.
2026-03-22 Fixing test
2026-04-07 switching to internal LSM6DSOX IMU feature for overstroke detection
2026-04-09 fixed the fans
2026-04-09 reorganizing modules
2026-04-29 Still some ACS issues
2026-06-08 misc changes
